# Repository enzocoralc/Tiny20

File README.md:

# Tiny20
Small and compact 20-keys keyboard

This is the current revision of the Tiny20 keyboard. It uses regular choc spacing and a promicro-compatible board. It's also compatible with both TRS and TRRS connectors and has a power switch and battery pads for easier wireless implementation.

I've also made a xiao-ble compatible board. It also has TRS and TRRS connector if you want to use a regular xiao board instead.

This is the current version of the chopped minis pcb, it's still in development.

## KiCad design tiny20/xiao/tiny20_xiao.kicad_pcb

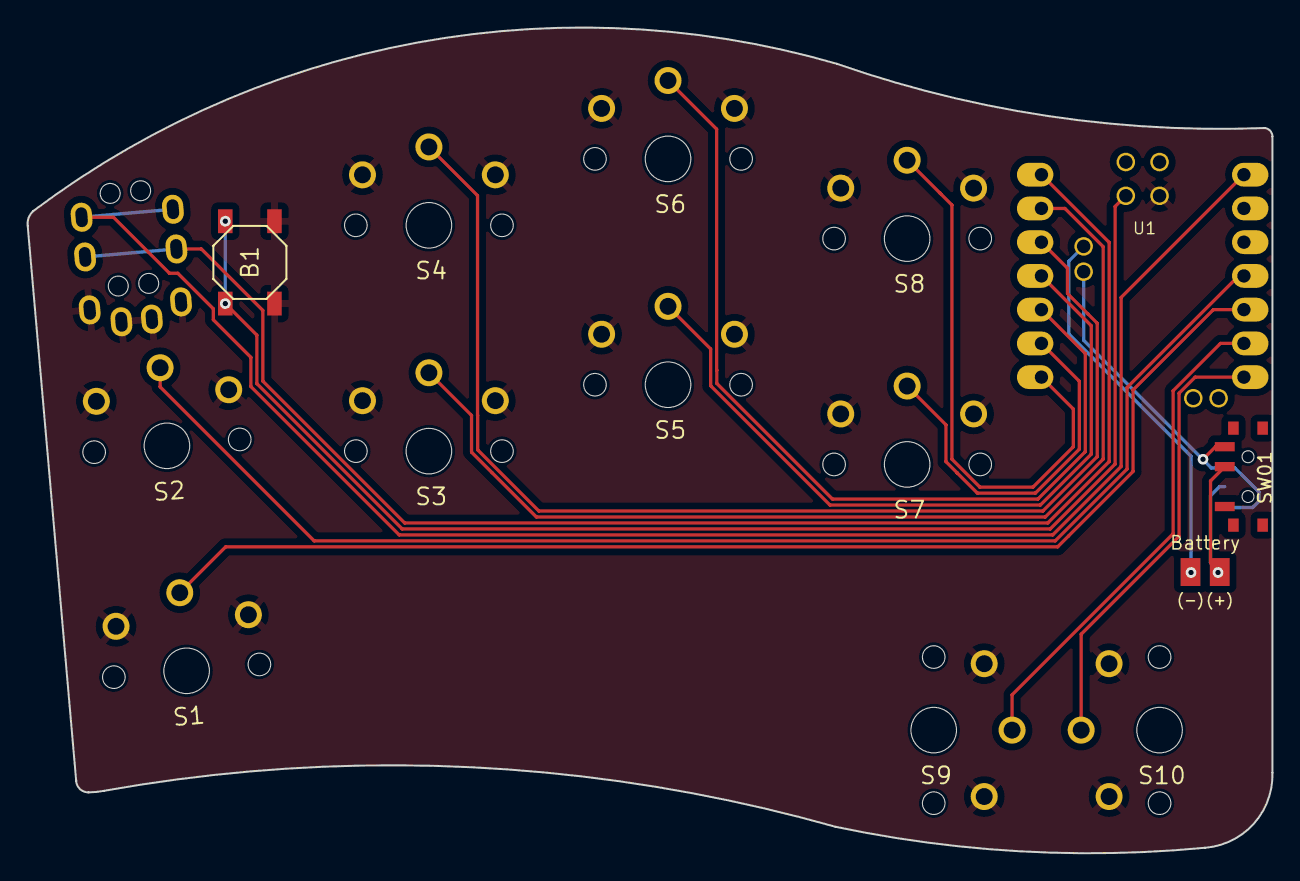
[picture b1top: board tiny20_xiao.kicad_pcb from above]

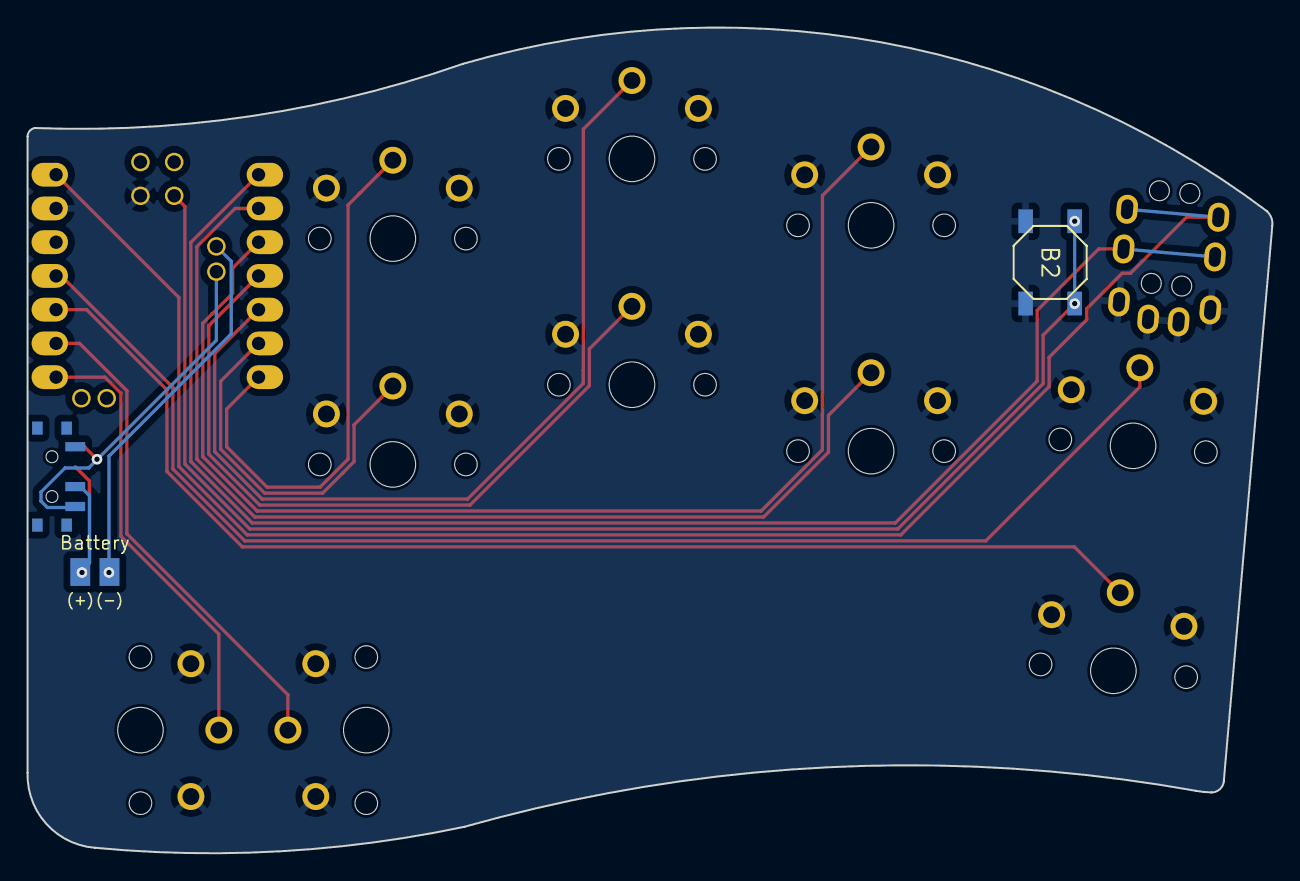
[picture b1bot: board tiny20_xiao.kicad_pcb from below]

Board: 2 copper layers, 93.7 x 62.2 mm, 16 parts (2 on the bottom side), 17 nets.

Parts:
B1, B2: SW_TACT_ALPS_SKQGABE010
BT01: Battery_Cell; battery_pads_reversible
S1, S2, S3, S4, S5, S6, S7, S8, S9, S10: chocV1_reversible
SW01: SW_SPDT; Power_reversible
TRRS: TRRS-PJ-320A-dual; TRS
U1: xiao-ble-thruhole; xiao-ble-tht

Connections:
5V: TRRS.4, U1.14
GND: B1.2, B2.2, S1.1, S2.1, S3.1, S4.1, S5.1, S6.1, S7.1, S8.1, S9.1, S10.1, TRRS.1, TRRS.2, U1.13, U1.18
P1: TRRS.3, U1.1
P2: S3.2, U1.2
P3: S4.2, U1.3
P4: S5.2, U1.4
P5: S6.2, U1.5
P6: S7.2, U1.6
P7: S8.2, U1.7
P8: S10.2, U1.8
P9: S9.2, U1.9
P10: S1.2, U1.10
P11: S2.2, U1.11
P19: SW01.3, U1.19
P20: BT01.2, U1.20
RST: B1.1, B2.1, U1.17
pm: BT01.1, SW01.2

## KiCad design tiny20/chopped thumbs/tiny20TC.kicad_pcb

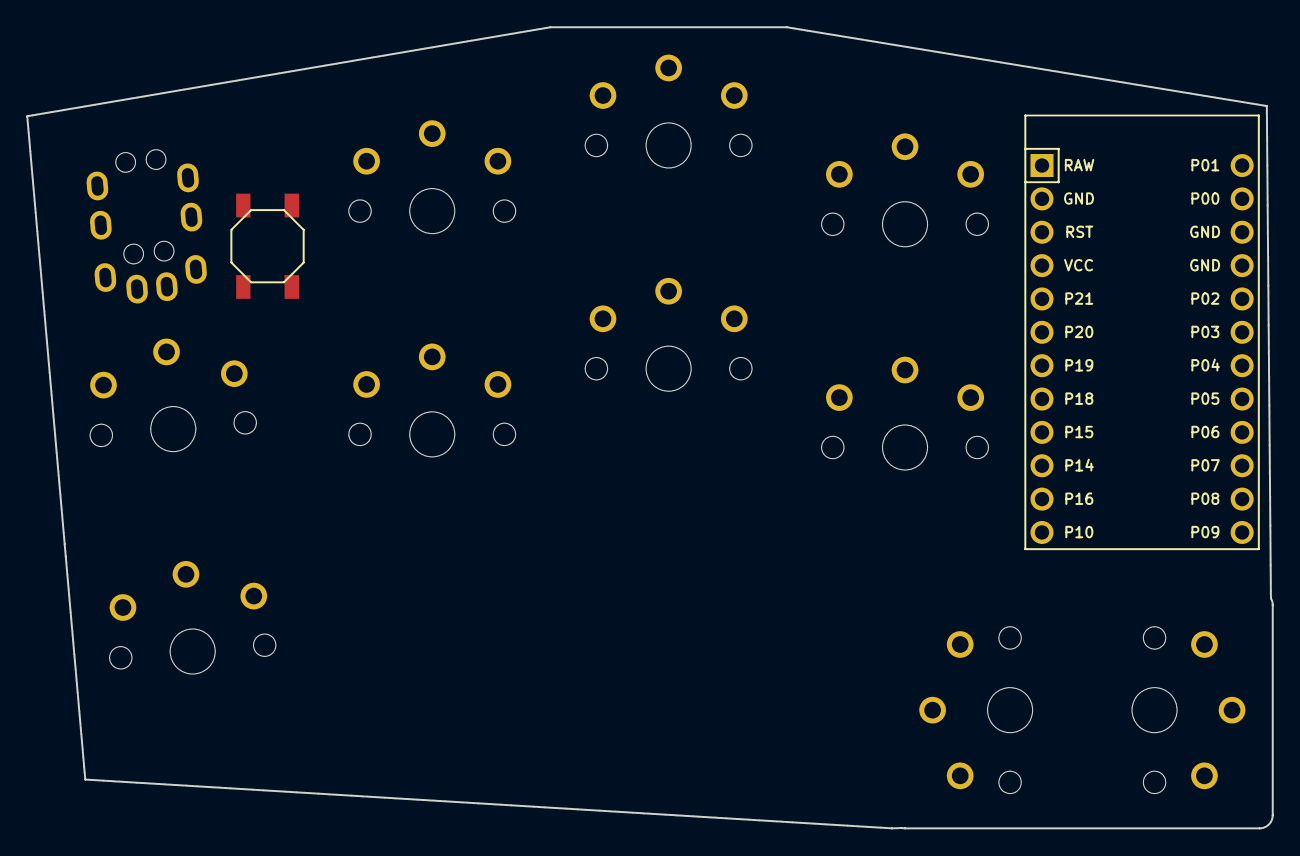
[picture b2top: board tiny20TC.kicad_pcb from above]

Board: 2 copper layers, 94.8 x 61.0 mm, 13 parts (0 on the bottom side), 12 nets, no tracks yet.

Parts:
B1, B2: SW_TACT_ALPS_SKQGABE010
MCU1: ProMicro
S1, S2, S3, S4, S5, S6, S7, S8, S9, S10: PG1350

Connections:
GND: B1.2, B2.2, MCU1.2, MCU1.15, MCU1.16, S1.2, S2.2, S3.2, S4.2, S5.2, S6.2, S7.2, S8.2, S9.2, S10.2
P1: MCU1.13, S1.1
P2: MCU1.17, S2.1
P3: MCU1.18, S3.1
P4: MCU1.19, S4.1
P5: MCU1.20, S5.1
P6: MCU1.21, S6.1
P7: MCU1.22, S7.1
P8: MCU1.23, S8.1
P9: MCU1.24, S10.1
P10: MCU1.12, S9.1
RST: B1.1, B2.1, MCU1.3

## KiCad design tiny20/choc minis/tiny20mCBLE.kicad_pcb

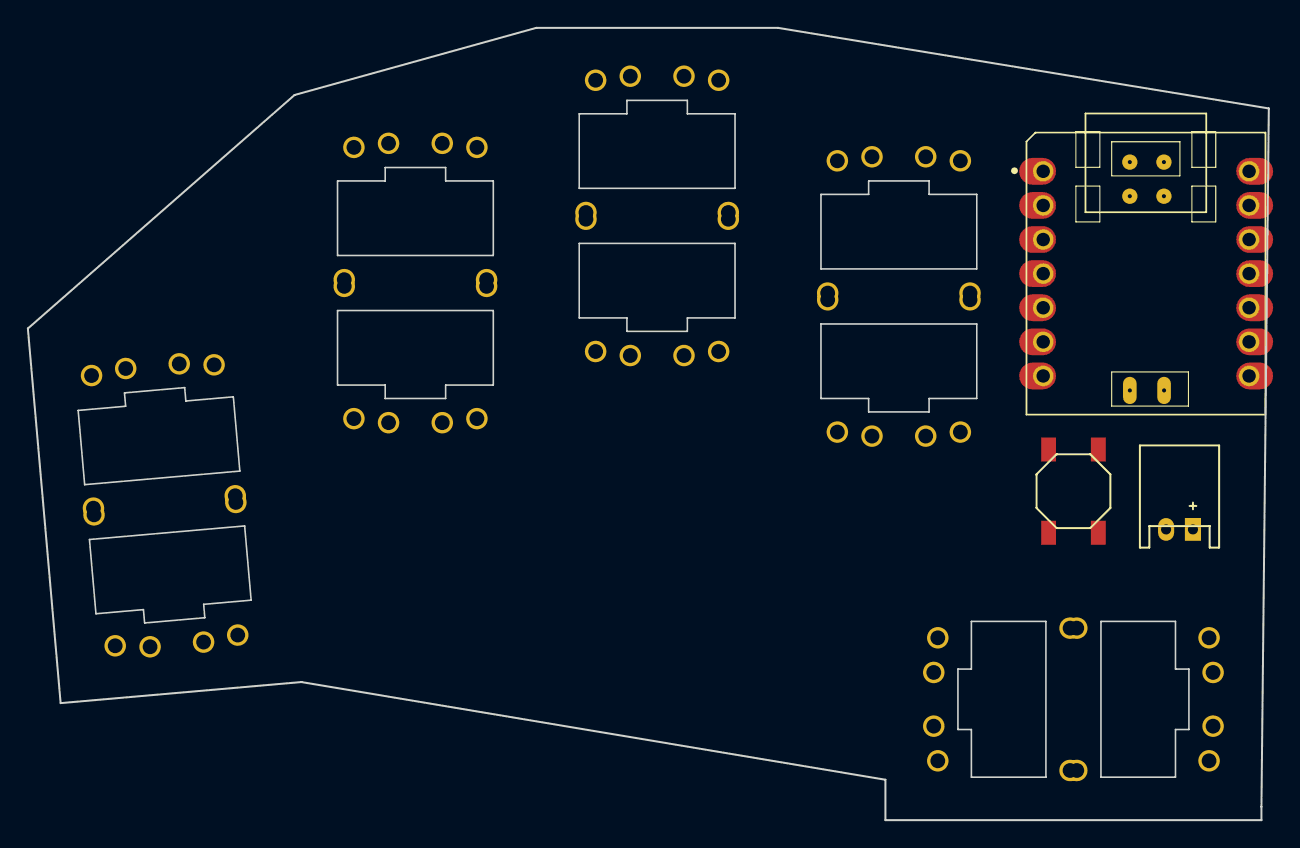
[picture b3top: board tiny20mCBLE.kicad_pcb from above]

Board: 2 copper layers, 92.4 x 59.0 mm, 13 parts (0 on the bottom side), 2 nets, no tracks yet.

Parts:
B1, B2: SW_TACT_ALPS_SKQGABE010
JST1: JST_PH_S2B-PH-K_02x2.00mm_Angled
S1, S2, S3, S4, S5, S6, S7, S8, S9, S10: Kailh_PG1232

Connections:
GND: B1.2, B2.2, JST1.2, S1.2, S2.2, S3.2, S4.2, S5.2, S6.2, S7.2, S8.2, S9.2, S10.2
RST: B1.1, B2.1

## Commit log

2021-11-23 added a few test layouts with chocs and chocs mini. And with primicro or xiao compatible footprints.
2021-11-23 added the KLE version for visual representation and the qmk compatible firmware for the gh60_satan
2021-11-23 added pcbV1 image for the readme
2021-11-23 updated the KLE files
2021-11-23 added images to the readme file
2021-11-23 improved mouse layer
2021-11-23 updated KLE version with the new mouse keymap
2021-11-23 fixed qmk mouse layer
2021-11-23 deleted old qmk directory to keep notation coherent
2021-11-23 updated kle version
2022-01-24 added gerbers for the chopped version
2022-02-09 added stuff
2022-04-19 updated the pcb
    Regular choc spacing board is finished with a new edgecut and promicro compatibility
2022-08-12 added xiao-BLE version
2022-08-14 added xiao-ble pic
2022-08-17 fixed the gerbers and BOM file for the xiao version
2022-08-24 fixed pcb stuff
2022-09-18 added the current KLE and zmk-firmware build
